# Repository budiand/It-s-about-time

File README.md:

# Proiect - It's about time!

## Realizare schematic:

Cu ajutorul fișierului [hector_watch.pdf](https://ocw.cs.pub.ro/courses/_media/tsc/hector_watch.pdf) ce conține indicații, a fost realizat schematic-ul. Deoarece butoanele și conectorul LCD din biblioteca de mai sus nu respectă anumite criterii, a fost necesară desenarea footprint-urilor acestora și atașarea într-o nouă bibliotecă. Corectitudinea a fost verificată folosind ERC.

## Realizare board:

Primul pas a fost decuparea PCB-ului, astfel încât acesta să respecte indicațiile de măsură (diam = 36mm). Primele componente așezate pe board au fost modulul ESP, conectorul USB C și butoanele, deoarece acestea sunt cele mai restrictive. Așezarea celorlalte componente s-a realizat ținând cont de numărul de semnale din circuit, astfel că numărul cel mai mare de semnale a avut prioritate. Traseele au fost rutate astfel încât să se respecte anumite constrângeri și reguli de "good practice" precum: evitarea intersectării traseelor, evitarea unghiurilor drepte, și altele. În final a fost realizată verificarea DRC cu succes.

## Probleme întâmpinate:

- Din cauza numărului mare de componente și a spațiului restrâns, au fost necesare mai multe încercări pentru a realiza o așezare optimă a componentelor.
- Realizarea footprint-urilor pentru butoane și pentru conectorul LCD a fost dificilă, deoarece a necesitat măsurători precise și ajustări.

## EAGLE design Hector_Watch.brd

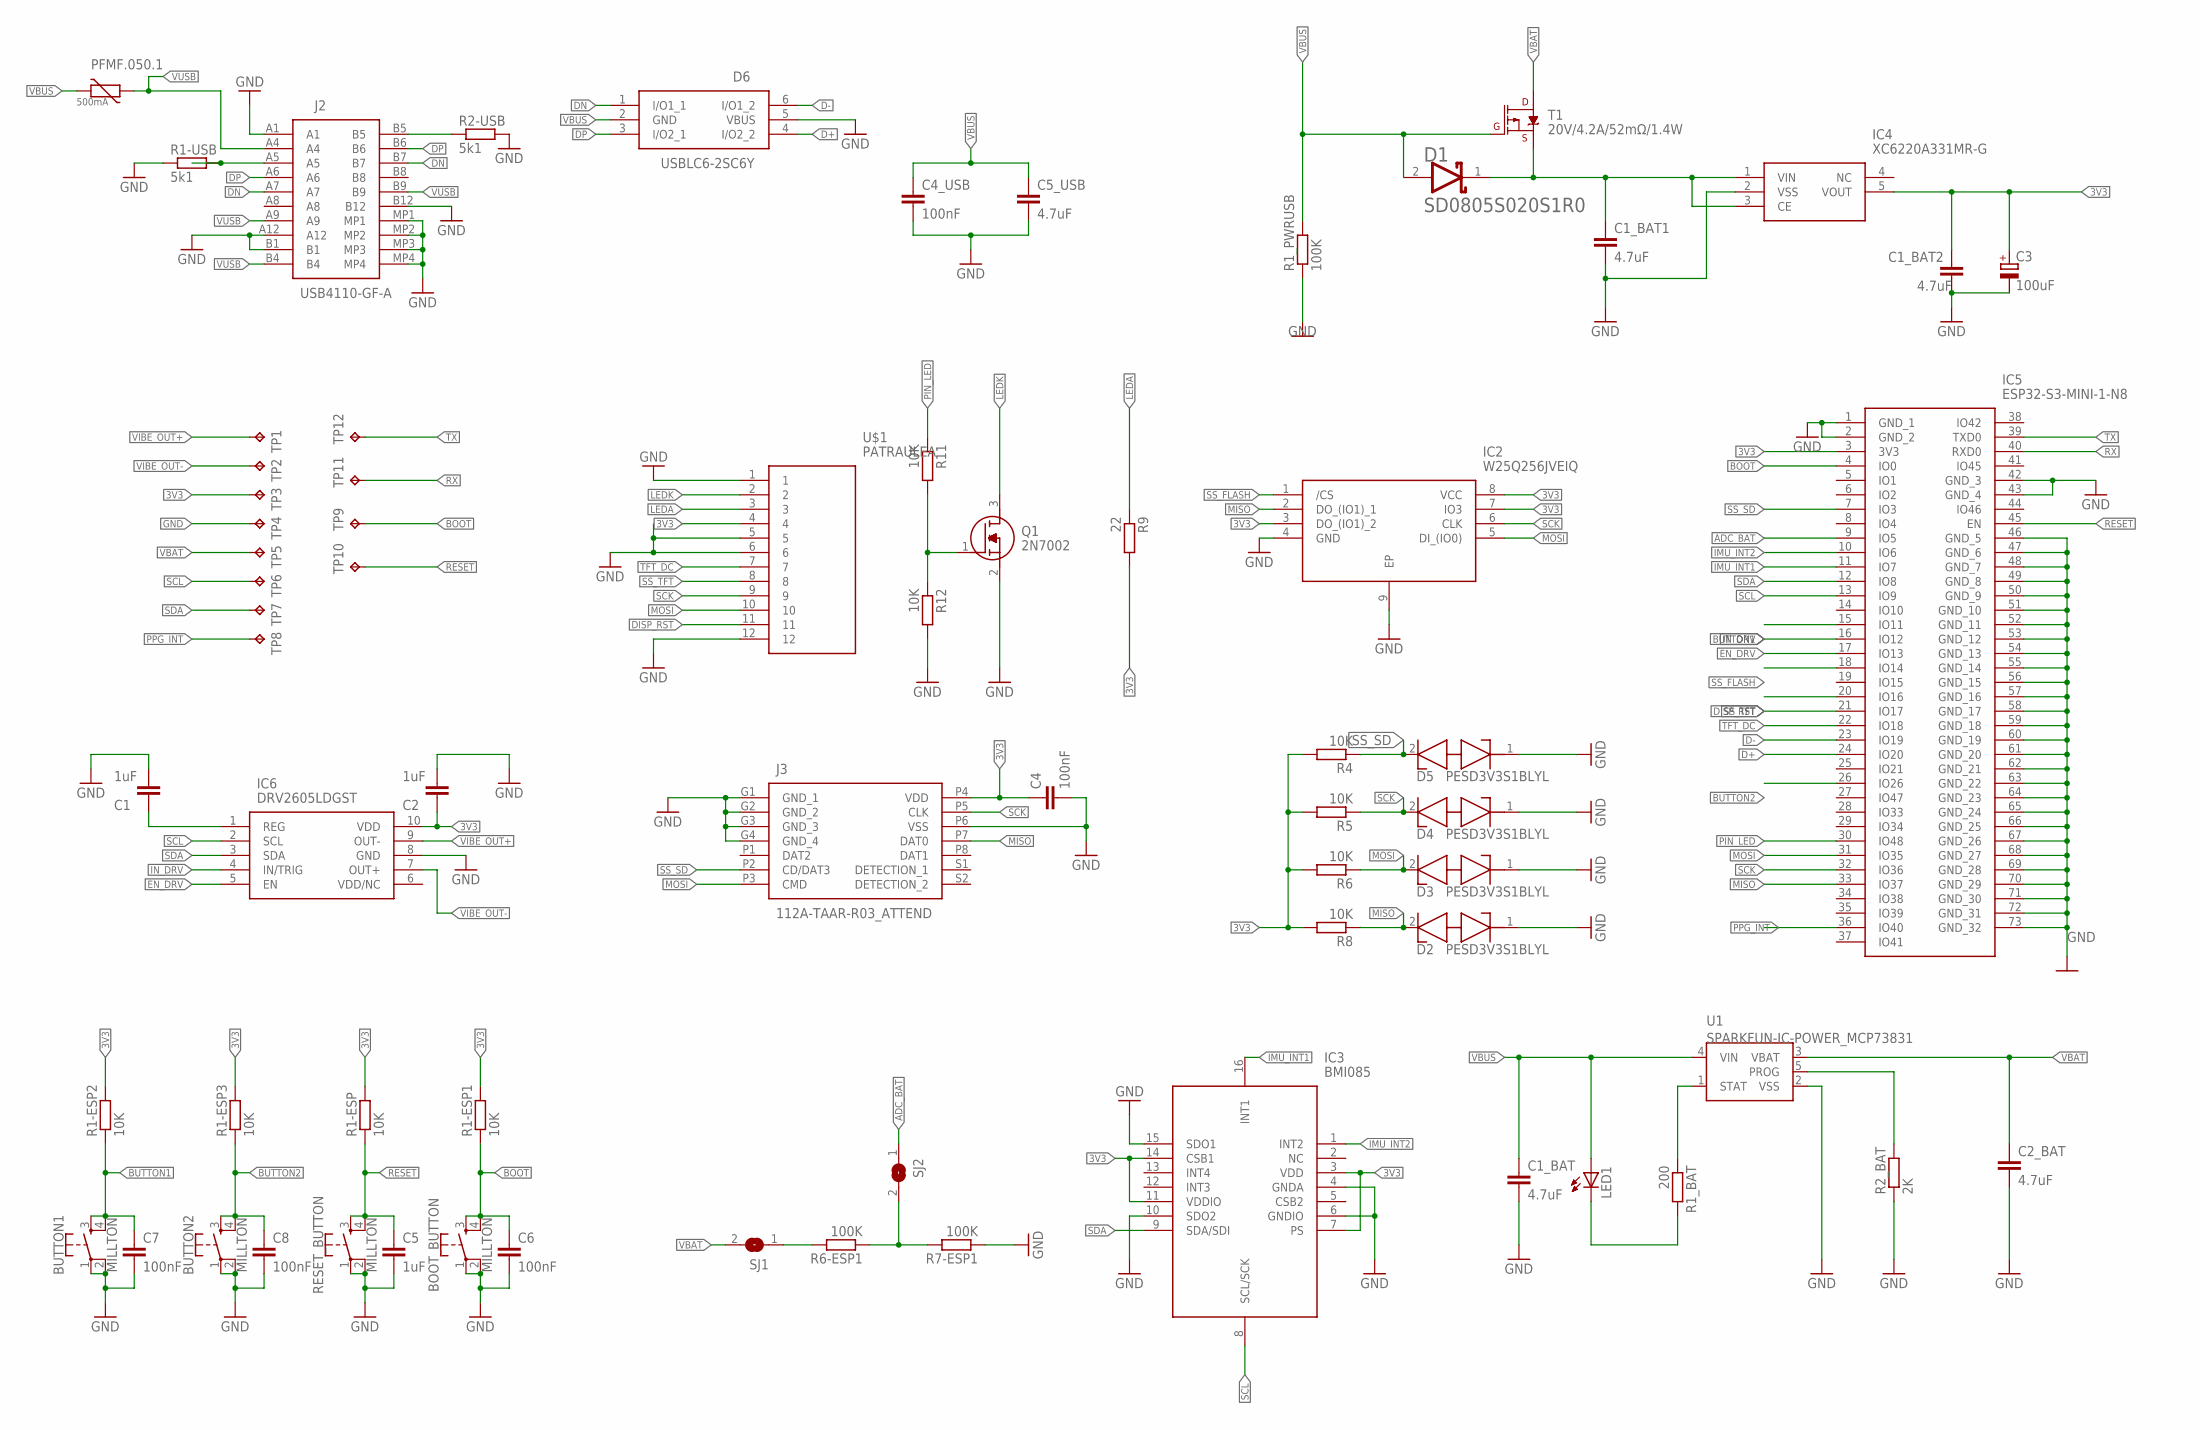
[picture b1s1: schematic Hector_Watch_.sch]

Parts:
BOOT_BUTTON: MILLTON
BUTTON1, BUTTON2: MILLTON
C1, C2, C5: 1uF; EAGLE-LTSPICE_C0402
C1_BAT, C1_BAT1, C1_BAT2, C2_BAT, C5_USB: 4.7uF; RCL_C0603
C3: 100uF; CT3528
C4, C6, C7, C8: 100nF; EAGLE-LTSPICE_C0402
C4_USB: 100nF; RCL_C0603
D1: AVX---SD0805S020S1R0_AVX_SD0805S020S1R0AVX_SD0805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; AVX---SD0805S020S1R0_AVX_SD0805S020S1R0_0
D2, D3, D4, D5: PESD3V3S1BLYL; PESD5V0S1BL315
D6: USBLC6-2SC6Y; SOT95P280X145-6N
IC2: W25Q256JVEIQ; SON127P800X600X80-9N
IC3: BMI085
IC4: XC6220A331MR-G; SOT95P280X120-5N
IC5: ESP32-S3-MINI-1-N8; ESP32S3MINI1N8
IC6: DRV2605LDGST; SOP50P490X110-10N
J2: USB4110-GF-A; USB4110GFA
J3: 112A-TAAR-R03_ATTEND; 112ATAARR03ATTEND
LED1: ADAFRUIT_LEDCHIP-LED0603; ADAFRUIT_CHIP-LED0603
PFMF.050.1: VARISTOR_VARISTORCN1812; VARISTOR_CT/CN1812
Q1: 2N7002; SOT96P240X120-3N
R1-ESP, R1-ESP1, R1-ESP2, R1-ESP3, R4, R5, R6, R8, R11, R12: 10K; EAGLE-LTSPICE_R0402
R1-USB, R2-USB: 5k1; EAGLE-LTSPICE_R0402
R1_BAT: 200; EAGLE-LTSPICE_R0402
R1_PWRUSB, R6-ESP1, R7-ESP1: 100K; EAGLE-LTSPICE_R0402
R2_BAT: 2K; EAGLE-LTSPICE_R0402
R9: 22; EAGLE-LTSPICE_R0402
RESET_BUTTON: MILLTON
SJ1, SJ2: SJ
T1: 20V/4.2A/52mΩ/1.4W; SPARKFUN-DISCRETESEMI_SOT23-3
TP1, TP2, TP3, TP4, TP5, TP6, TP7, TP8, TP9, TP10, TP11, TP12: TPTP20R; TP20R
U1: SPARKFUN-IC-POWER_MCP73831; SPARKFUN-IC-POWER_SOT23-5
U$1: PATRAULEA; PCA6LA12HL3TR

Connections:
3V3: C1_BAT2.1, C2.2, C3.+, C4.1, IC2.3 (DO_(IO1)_2), IC2.7 (IO3), IC2.8 (VCC), IC3.3 (VDD), IC3.7 (PS), IC3.11 (VDDIO), IC3.14 (CSB1), IC4.5 (VOUT), IC5.3 (3V3), IC6.10 (VDD), J3.P4 (VDD), R1-ESP.2, R1-ESP1.2, R1-ESP2.2, R1-ESP3.2, R4.2, R5.2, R6.2, R8.2, R9.2, TP3.TP, U$1.4
ADC_BAT: IC5.9 (IO5), SJ2.1
BOOT: BOOT_BUTTON.3, BOOT_BUTTON.4, C6.1, IC5.4 (IO0), R1-ESP1.1, TP9.TP
BUTTON1: BUTTON1.3, BUTTON1.4, C7.1, IC5.15 (IO11), R1-ESP2.1
BUTTON2: BUTTON2.3, BUTTON2.4, C8.1, IC5.26 (IO26), R1-ESP3.1
D+: D6.4 (I/O2_2), IC5.24 (IO20)
D-: D6.6 (I/O1_2), IC5.23 (IO19)
DISP_RST: IC5.20 (IO16), U$1.11
DN: D6.1 (I/O1_1), J2.A7, J2.B7
DP: D6.3 (I/O2_1), J2.A6, J2.B6
EN_DRV: IC5.17 (IO13), IC6.5 (EN)
GND: BOOT_BUTTON.1, BOOT_BUTTON.2, BUTTON1.1, BUTTON1.2, BUTTON2.1, BUTTON2.2, C1.1, C1_BAT.2, C1_BAT1.2, C1_BAT2.2, C2.1, C2_BAT.2, C3.-, C4.2, C4_USB.2, C5.2, C5_USB.2, C6.2, C7.2, C8.2, D2.1 (K1), D3.1 (K1), D4.1 (K1), D5.1 (K1), D6.5 (VBUS), IC2.4 (GND), IC2.9 (EP), IC3.4 (GNDA), IC3.6 (GNDIO), IC3.10 (SDO2), IC3.15 (SDO1), IC4.2 (VSS), IC5.1 (GND_1), IC5.2 (GND_2), IC5.42 (GND_3), IC5.43 (GND_4), IC5.46 (GND_5), IC5.47 (GND_6), IC5.48 (GND_7), IC5.49 (GND_8), IC5.50 (GND_9), IC5.51 (GND_10), IC5.52 (GND_11), IC5.53 (GND_12), IC5.54 (GND_13), IC5.55 (GND_14), IC5.56 (GND_15), IC5.57 (GND_16), IC5.58 (GND_17), IC5.59 (GND_18), IC5.60 (GND_19), IC5.61 (GND_20), IC5.62 (GND_21), IC5.63 (GND_22), IC5.64 (GND_23), IC5.65 (GND_24), IC5.66 (GND_25), IC5.67 (GND_26), IC5.68 (GND_27), IC5.69 (GND_28), IC5.70 (GND_29), IC5.71 (GND_30), IC5.72 (GND_31), IC5.73 (GND_32), IC6.8 (GND), J2.A1, J2.A12, J2.B1, J2.B12, J2.MP1, J2.MP2, J2.MP3, J2.MP4, J3.G1 (GND_1), J3.G2 (GND_2), J3.G3 (GND_3), J3.G4 (GND_4), J3.P6 (VSS), Q1.2 (S), R1-USB.1, R1_PWRUSB.1, R2-USB.2, R2_BAT.1, R7-ESP1.1, R12.2, RESET_BUTTON.1, RESET_BUTTON.2, TP4.TP, U1.2 (VSS), U$1.1, U$1.5, U$1.6
IMU_INT1: IC3.16 (INT1), IC5.11 (IO7)
IMU_INT2: IC3.1 (INT2), IC5.10 (IO6)
IN_DRV: IC5.16 (IO12), IC6.4 (IN/TRIG)
LEDA: R9.1, U$1.3
LEDK: Q1.3 (D), U$1.2
MISO: D2.2 (K2), IC2.2 (DO_(IO1)_1), IC5.33 (IO37), J3.P7 (DAT0), R8.1
MOSI: D3.2 (K2), IC2.5 (DI_(IO0)), IC5.31 (IO35), J3.P3 (CMD), R6.1, U$1.10
unnamed: Q1.1 (G), R11.2, R12.1
unnamed: C1.2, IC6.1 (REG)
unnamed: J2.A5, R1-USB.2
unnamed: R6-ESP1.1, R7-ESP1.2, SJ2.2
unnamed: C1_BAT1.1, D1.1 (CATHODE), IC4.1 (VIN), IC4.3 (CE), T1.2 (S)
unnamed: R6-ESP1.2, SJ1.1
unnamed: LED1.C, R1_BAT.2
unnamed: R2_BAT.2, U1.5 (PROG)
unnamed: J2.B5, R2-USB.1
unnamed: R1_BAT.1, U1.1 (STAT)
PIN_LED: IC5.30 (IO48), R11.1
PPG_INT: IC5.36 (IO40), TP8.TP
RESET: C5.1, IC5.45 (EN), R1-ESP.1, RESET_BUTTON.3, RESET_BUTTON.4, TP10.TP
RX: IC5.40 (RXD0), TP11.TP
SCK: D4.2 (K2), IC2.6 (CLK), IC5.32 (IO36), J3.P5 (CLK), R5.1, U$1.9
SCL: IC3.8 (SCL/SCK), IC5.13 (IO9), IC6.2 (SCL), TP6.TP
SDA: IC3.9 (SDA/SDI), IC5.12 (IO8), IC6.3 (SDA), TP7.TP
SS_FLASH: IC2.1 (/CS), IC5.18 (IO14)
SS_SD: D5.2 (K2), IC5.7 (IO3), J3.P2 (CD/DAT3), R4.1
SS_TFT: IC5.21 (IO17), U$1.8
TFT_DC: IC5.22 (IO18), U$1.7
TX: IC5.39 (TXD0), TP12.TP
VBAT: C2_BAT.1, SJ1.2, T1.3 (D), TP5.TP, U1.3 (VBAT)
VBUS: C1_BAT.1, C4_USB.1, C5_USB.1, D1.2 (ANODE), D6.2 (GND), LED1.A, PFMF.050.1.2, R1_PWRUSB.2, T1.1 (G), U1.4 (VIN)
VIBE_OUT+: IC6.9 (OUT-), TP1.TP
VIBE_OUT-: IC6.7 (OUT+), TP2.TP
VUSB: J2.A4, J2.A9, J2.B4, J2.B9, PFMF.050.1.1

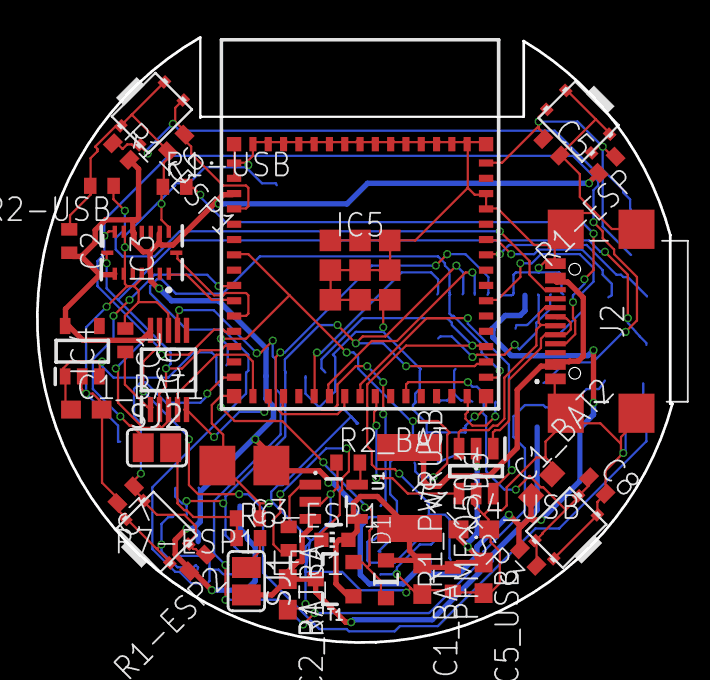
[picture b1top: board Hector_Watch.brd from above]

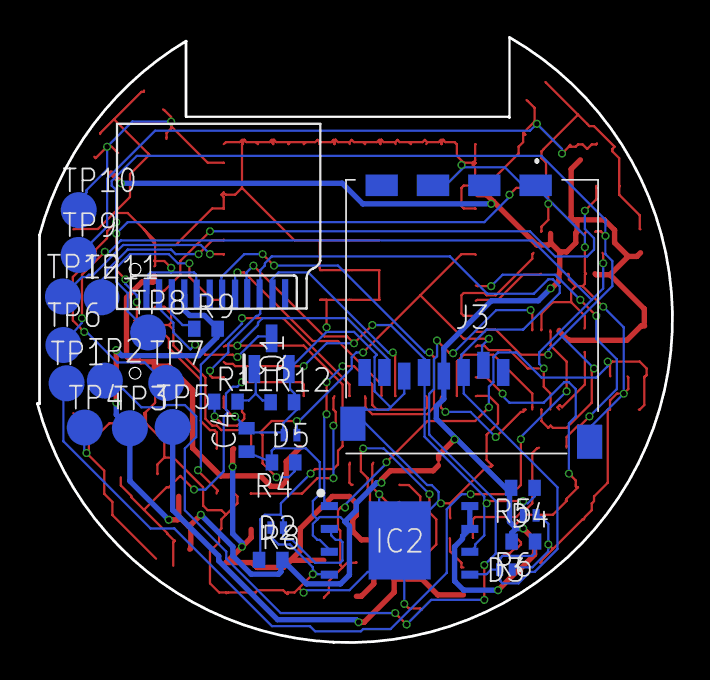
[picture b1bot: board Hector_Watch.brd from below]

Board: 2 copper layers, 35.3 x 33.6 mm, 69 parts (28 on the bottom side), 46 nets.
